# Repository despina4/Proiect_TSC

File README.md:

# Documentatie Hardware - Proiect Wearable / Smartwatch nRF52840

## 1. Diagrama Bloc

Diagrama ilustreaza doua fluxuri principale:
*   **Fluxul de Alimentare:** De la portul USB-C, prin circuitul de incarcare, catre baterie si apoi prin convertorul DC/DC catre restul componentelor.
*   **Fluxul de Date/Control:** Centrat pe microcontrolerul nRF52840, care comunica cu senzorii, display-ul.

---

## 2. Bill of Materials (BOM)

Tabelul de mai jos contine modulele principale folosite in proiect, impreuna cu link-uri pentru achizitie si specificatii tehnice.

| Nume produs | Ref | Link achizitionare | Datasheet |
| :--- | :--- | :--- | :--- |
| **nRF52840-QIAA** | U1 | [Component Search Engine](https://componentsearchengine.com/part-view/NRF52840-QIAA-R/Nordic%20Semiconductor) | [Datasheet](https://4donline.ihs.com/images/VipMasterIC/IC/NRSA/NRSA-S-A0021008244/NRSA-S-A0021008244-1.pdf?hkey=61A2E4C270F0397D049F8F05BD4F1054) |
| **BQ25180YBGR** | IC1 | [Component Search Engine](https://componentsearchengine.com/search?term=BQ25180YBGR) | [Datasheet](https://analytics.supplyframe.com/trackingservlet/track/?r=0x34EY99PS_gIu2qWuzU9_U842M9-un2szqNoXX0OQ9lqbiEKGN3BJ73jgvlrgiXR89Peb0evqc4GXoUXllBhv0EBbS6IvP2J9XlK2jP2A6stFn-y2dC_JwPYaasEzx0O-vxRsHrvjDMttJo6_R4oFWH3JMP3HPT3L-Nznne1h3KEsMXPl-eGs-pMLJ6GfjQCQ6HQMtq6htuNY6F9LyUZPlBJcp1K0CY8wZlcmYWeP3d00EKGkwMEYVuhGukZlpk9s5eB2sCQiAmMMBIBl2JypaU6-1_JfgzrT5bvUUGSdkUqZVMi7lvw7V03cGienT9feVSRMBhhWaNFGhzf6_3f8ZFIsqpCB6RNiXgzOy4UCL8GWfRIZFBGLsZvpqmkT4iLPnvXUrdv-uMDsMargLsNudyjFN55qoFIoM_lHR3jfZiBrXHrx7fYI1m3zFYuPc18lUM4dLxlLjbOFrCL0NYDVpEveG92dFwHfnYbXQgvjrXr2rAOwFVNwEcAFSYk5ktGr0AZVSeLG20ATU9f5Ua1VPDIn7dlK_upDe2HQ7ZnA50hRZ6l5EHTT1TR6mV6zah) |
| **DRV2605YZFR** | IC2 | [Component Search Engine](https://componentsearchengine.com/search?term=DRV2605YZFR) | [Datasheet](https://analytics.supplyframe.com/trackingservlet/track/?r=0x34EY99PS_gIu2qWuzU9_U842M9-un2szqNoXX0OQ9lqbiEKGN3BJ73jgvlrgiXR89Peb0evqc4GXoUXllBhv0EBbS6IvP2J9XlK2jP2A5_GZUU6ZJYL2OifsViLlEfO-vxRsHrvjDMttJo6_R4oFWH3JMP3HPT3L-Nznne1h3KEsMXPl-eGs-pMLJ6GfjQCQ6HQMtq6htuNY6F9LyUZPlBJcp1K0CY8wZlcmYWeP0ge5YXjaukObe0lIq9YZ1Y9s5eB2sCQiAmMMBIBl2JytG3z6cPnGe-cmO7h9dQIJ2kzUBKYJ3kKq1ql5kAIW4INEEo_wOFAtAhver6Q6kuIfVofA0tjpG_oIZ517f4Vb78GWfRIZFBGLsZvpqmkT4iLPnvXUrdv-uMDsMargLsNnX2hKYawPQ2D7SudtAUHHtiBrXHrx7fYI1m3zFYuPc18lUM4dLxlLjbOFrCL0NYDVpEveG92dFwHfnYbXQgvjrXr2rAOwFVNwEcAFSYk5ktqoT45GaC_RMx31tbcd0eeVPDIn7dlK_upDe2HQ7ZnA50hRZ6l5EHTT1TR6mV6zah) |
| **BMA423** | IC3 | [Component Search Engine](https://componentsearchengine.com/search?term=bma423) | [Datasheet](https://analytics.supplyframe.com/trackingservlet/track/?r=0x34EY99PS_gIu2qWuzU9_U842M9-un2szqNoXX0OQ9lqbiEKGN3BJ73jgvlrgiXR89Peb0evqc4GXoUXllBhv0EBbS6IvP2J9XlK2jP2A65Hh8cz60QZRR0eH2YQezA3QFuEZVrF44_bcvGN_lyh23KGb2OV452gy8_0y5ECrz838JB1AXz4HlagHjHKK0zIVUI_nXq20DP4qZVoZkXjzWM81fZaYscHPt3_tBNEt3RrwddE0Gz5nohvYrd6gxYc3LSeSqEPukqMV5glPuL1CNaI1kVMusAxJjzUp0G6CswwJW_ssfKVIHLQT-IJeMMwbXLDJpduD2PNPjtLS0y1srGxUCiKdKyCV91htNfRSMP3qWp9KAByolyr1E2K_PZ5B6aRPZ6alq5MnvhLx7KzpSpvK4vdnUllhspAmNRIPTvgHjblUHXdwUjCbyASDYb9MYvdijqaUwAnHrJsf3zmbjzHXjtwLXVovtyhuM6e6Ynw7vpRUSsWu0xJF95B32liScqep17qvTwnJG7pQnxHSR6-2eSgXb3qFP3Jk0Oamw51BA5ruLDXxwczn9SmJ5bdh_kmzVEzIYo-AC-eZSsAdcBnfKHuYtpsSdnOr0On6uXkGbg_xWe6X4FW8arIIpH) |
| **RT6160AWSC** | IC9 | [Component Search Engine](https://componentsearchengine.com/part-view/RT6160AWSC/RICHTEK) | [Datasheet](https://analytics.supplyframe.com/trackingservlet/track/?r=0x34EY99PS_gIu2qWuzU9_U842M9-un2szqNoXX0OQ9lqbiEKGN3BJ73jgvlrgiXR89Peb0evqc4GXoUXllBhv0EBbS6IvP2J9XlK2jP2A7oxjHvu3vjqv4WxQoBIehIpFdNxUOLInPyEkIhtPddHwvaXQpBCG-4NPHWS8Luf9PDHBq8VAfKRDCu-t4VKkJgw0q36_CHuXBQmQUFy7_kW1dsUOzQneFlP07hp6tEqIRtrF0F5Zb_nR1t-hLLccIBUGxWBuEpEl7kUFZ6dE5hS-7kEI0Imii-UkRj2fTw2ElN8-A1nBG9hKzVKn06I4IowPKk5xXTOIwLAB724T4UUPVC2PjCMrZrSZdNsHPTjWe6k3zgMkqRJAhHbiU-gTTV8piVEtXZSzcLQMzYFvj83r7hfL_VtnnBJVZtCWXJKkLcTeL-qC6Kw-bbZFGwqn1eTorqzedjC01O_9x4TSWbk5yQDrvZUK-iGRXtGqr6qwa0P7iXpgr0HPlvis6ez45oylOW77ENVj4BRgrI885Q_XvOL-xgY1EhwCaKTrd3oN5is0EaxHlNGM4zz0QyxhvBvl-geXlL_R-njMpWcd0RKFtHWMev1NGVlnzxgiu0SjMG-5Cr55kPMae_7V9Vf5dfvXk1u41AF-eDZgjn1NFilA) |
| **MAX17048G+** | U3 | [Component Search Engine](https://componentsearchengine.com/part-view/MAX17048G%2B/Analog%20Devices) | [Datasheet](https://analytics.supplyframe.com/trackingservlet/track/?r=0x34EY99PS_gIu2qWuzU9_U842M9-un2szqNoXX0OQ9lqbiEKGN3BJ73jgvlrgiXR89Peb0evqc4GXoUXllBhv0EBbS6IvP2J9XlK2jP2A6DXbvJdRmZW2yJtFQ1_uB8CpVVRsuy5H3f7RjpWY5KE02ZSejBQ-1sTThh8ZhaVmPyvNMTfmvWqPHCxujzIU_9L5QMgSVsWqB7UcVIWqkZMCBUsKvx5VN_Ff7UgqURIux-A-P-bJZx2uYoMIaFEdYZKxLQSmqRADJVv0bC3pADlsMXLGPj7wuD_4oozecdZ0K-8Axqnk-A4H62ngUFyJ-u_KU29-JDjkr_a4X5kD-SwJaXo8CyXJYulMKyYA9Ww-0YTP0WJ4WexDOETYGOo7QYWrTP3cuO2jaBxtmnP_QmXvwZZ9EhkUEYuxm-mqaRPiIs-e9dSt2_64wOwxquAuw2wbj8YtdMq1G5JGMGXucSqWIGtcevHt9gjWbfMVi49zXyVQzh0vGUuNs4WsIvQ1gNWkS94b3Z0XAd-dhtdCC-OtevasA7AVU3ARwAVJiTmS3yOHNszfnmm1dqoJi-2CiH_5iJolc-gxDtjl0RWrOjUc2y34iccbFKo6BQ_BAC8ZA) |
| **USB4105-GF-A** | J4 | [SnapMagic](https://www.snapeda.com/parts/USB4105-GF-A/GCT/view-part/?ref=search&t=USB4105-GF-A&ab_test_case=b) | [Datasheet](https://www.snapeda.com/parts/USB4105-GF-A/GCT/datasheet/) |
| **503480-2400** | J1 | [Component Search Engine](https://componentsearchengine.com/part-view/503480-2400/Molex) | [Datasheet](https://analytics.supplyframe.com/trackingservlet/track/?r=0x34EY99PS_gIu2qWuzU9_U842M9-un2szqNoXX0OQ9lqbiEKGN3BJ73jgvlrgiXR89Peb0evqc4GXoUXllBhv0EBbS6IvP2J9XlK2jP2A4bhBcp5m93QVvXq-b4ZvXprUYNzIdppOCDGuJ7aDflaky8671aiqchDLLtbVjC9xdCaJJ6nF0pYtLKaCopUVPbENE6D3pzXoxhUvdbzuW6oJXfd1FVm63N6SPCyX6r1R5v9WVM0GlwVZLnxlj5hrMZy4odeEzEID3f9KwH_MHnqtKpOLWlH5R74gzWY8AYOo5GMjISf0eMdYvE6MODW1eb4kLz15caNHBYeIVK5MK9qSpUczJXWYrJFJGp6PnnEax_T5A32QcD4zvMW-ssnnZd4OhSZlAx9pe7i1e8hrw58wOHOyfVNVOXSLomvqnUeGmBnnj8VHAk7jgVz6Pxql9q4VLXOsw1zGQSjIjD0YczTpyQDrvZUK-iGRXtGqr6qwa0P7iXpgr0HPlvis6ez45oYMjPU0esZvj56AyDu6TV43vOL-xgY1EhwCaKTrd3oN5is0EaxHlNGM4zz0QyxhvBvl-geXlL_R-njMpWcd0RKFtHWMev1NGVlnzxgiu0SjM64VUgM7uRV37HYPQ2vpo0llXHrUb_2BeaRI1zgnEpSA) |
| **EVP-AKE31A** | SW_x | [Component Search Engine](https://componentsearchengine.com/part-view/EVPAKE31A/Panasonic) | [Datasheet](https://analytics.supplyframe.com/trackingservlet/track/?r=0x34EY99PS_gIu2qWuzU9_U842M9-un2szqNoXX0OQ9lqbiEKGN3BJ73jgvlrgiXR89Peb0evqc4GXoUXllBhv0EBbS6IvP2J9XlK2jP2A7jRNlQCGFKUCB9Om2oIPVb8wB-QC4Y0LpnCr5Xq_ByDC5GEiqgkeKxStY5Iu4CVibuldEG2BjB5lNvto04wXg8jGQATYHCL6DopdSbrdwi56E6tw2YzEoN2JK_GY31dBUUo3LDYzCtu7wIFWHSy5ldFUMm7nZxbAbVY0l3I7ewOZYX363B6_l_RD2rR4C4K-my9KZLIZBsuzkxb3A5MS3NsEKKVZJUvtL97I9b8a5mIzliD9eDRpt3ctCvjuas-AASRFTRlsq83k9cscG5Zi-TsUcA-0LBtlakk22B3qKjpagoB0KIBYTkXeQHEqE58jyRQGb7iM-fmdBd-zqmHjtKd_NmoHXgB5duqrDZJlY4H5yQDrvZUK-iGRXtGqr6qwa0P7iXpgr0HPlvis6ez45o2VHowPjIDZTEf8wGRQ4ci3vOL-xgY1EhwCaKTrd3oN5is0EaxHlNGM4zz0QyxhvBvl-geXlL_R-njMpWcd0RKFtHWMev1NGVlnzxgiu0SjOjOFfjEDKuI85CkEY44YiXAqRNgBm1QPZfXRUNd55gVA) |
| **2450AT18B100E** | ANT1 | [Component Search Engine](https://componentsearchengine.com/part-view/2450AT18B100E/JOHANSON%20TECHNOLOGY) | [Datasheet](https://analytics.supplyframe.com/trackingservlet/track/?r=0x34EY99PS_gIu2qWuzU9_U842M9-un2szqNoXX0OQ9lqbiEKGN3BJ73jgvlrgiXR89Peb0evqc4GXoUXllBhv0EBbS6IvP2J9XlK2jP2A5CBZpEZS1QpXV8FFu44G8mfHuYmg61LS2zWxuqTvB9fpXV375gtD9bFmcCH2H2-DAuRhIqoJHisUrWOSLuAlYmG3OIjmksJ1dRyGU5ZtR5ygKEZn7IXrj9HCDF2qCHjmkMrQBkA8LW1ZVPP8ECLfGEq3PUbV5s03lneGIiPby_jK-PplrsL5DHOAlCUT_Isuz2zl4HawJCICYwwEgGXYnKR7O9_Lww0zeRhLdSHLfmKLGvvXkZ69BbN2cqUVuLZwWkzHNmVRqmDRdD2bTu63RwJxUArrnlVYIvOowP0A2ooJyQDrvZUK-iGRXtGqr6qwa0P7iXpgr0HPlvis6ez45oA6DbeayHRodKseYDStLS-HvOL-xgY1EhwCaKTrd3oN5is0EaxHlNGM4zz0QyxhvBvl-geXlL_R-njMpWcd0RKFtHWMev1NGVlnzxgiu0SjN1C5tMR-D4l4QIlPKj2IZ-Yy9VWewJTIBnNBaBqDAucmok7ZMY6ahHbaLYDtLSQSg) |
| **02016D105KAT4A** | Cap | [Component Search Engine](https://componentsearchengine.com/part-view/02016D105KAT4A/Kyocera%20AVX) | [Datasheet](https://analytics.supplyframe.com/trackingservlet/track/?r=0x34EY99PS_gIu2qWuzU9_U842M9-un2szqNoXX0OQ9lqbiEKGN3BJ73jgvlrgiXR89Peb0evqc4GXoUXllBhv0EBbS6IvP2J9XlK2jP2A7nZAqH6w5fKchKrnD5jWCWB9uu1cFEpsbINa2EvY3xALGo-iAVS7h3PyuKIuP0uNZtyhm9jleOdoMvP9MuRAq8_N_CQdQF8-B5WoB4xyitMyFVCP516ttAz-KmVaGZF481jPNX2WmLHBz7d_7QTRLdwdqbPKSozx2UncdATv8f8tXMySboAvDMsIjBRKwEr_Q2jLNScnH_dLxDrjv1EkHNMMCVv7LHylSBy0E_iCXjDMG1ywyaXbg9jzT47S0tMtbKxsVAoinSsglfdYbTX0UjdS3r3VBQI1vaml90w1YXmOZwvE2zhk6aceLOkr7DbpYy5Q4LxAI48xDMx_XnZmHh_fuDZ1JjOvgaKgrvl3RWpnkNWF_MCUOTM_XXPqM7bQP8GWfRIZFBGLsZvpqmkT4iLPnvXUrdv-uMDsMargLsNqbHJnjKIKwWJs5Y8BBPlGdiBrXHrx7fYI1m3zFYuPc18lUM4dLxlLjbOFrCL0NYDVpEveG92dFwHfnYbXQgvjrXr2rAOwFVNwEcAFSYk5kt9N8XAFyUPAGbflqS7VyAcxuzNsnrGaIyGIlhKp9g4wTmDKwPnl8GHxC8271ufp6a) |
| **0402B472K500NT** | Cap | [Component Search Engine](https://componentsearchengine.com/part-view/0402B472K500NT/Guangdong%20Fenghua%20Advanced%20Tech) | [Datasheet](https://analytics.supplyframe.com/trackingservlet/track/?r=0x34EY99PS_gIu2qWuzU9_U842M9-un2szqNoXX0OQ9lqbiEKGN3BJ73jgvlrgiXR89Peb0evqc4GXoUXllBhv0EBbS6IvP2J9XlK2jP2A5dXweU-D0sdBl1Qjp1-TAk_mVbiV46egqumwUGPF1lPZOKh6TrHICN8puILsKgsK-sQYSYGHAdrwcZ8E3HkBuRqTzZoYvrcDuK6DczS8PHjtCeG-EZDmaKILRgGXnDovSJdSjTWfIdrOBLyjZVWwqbU8QHBZonHiX1ulf1ijnuV7zT-G6CvmssDKjz6ykjyiiOL6l3SGqOLFDw0gOobHbOqHuUYKiE61kjf205L08i3UM0rohfI1WiHrOQi4HMOm09cQB_Eb5GLgSyk-l9ROWJYnHwneW9h_i_wyqbadWvI2fq1mxS8j8a2gzW5h7Am3q22IuGOtCVzPmDh8SvQTkQ758gNK6-fDp2DK2st6xkFXHiipFVag1_ybNPdjfdaX1UzwWSBXnGX2GnGPz7GnffHFOReOLDLMKa5h6Mh-WEPbjzHXjtwLXVovtyhuM6e6bvcO-Aa1fTPjORUyGtfwzUiScqep17qvTwnJG7pQnxHSR6-2eSgXb3qFP3Jk0Oamw51BA5ruLDXxwczn9SmJ5bdh_kmzVEzIYo-AC-eZSsAe9gIh7dial-5XlJgFXLBC6nnoq1N-30oEqZ652mt86F5eSLo1vpaeRbZ2kk2sM_6fNceAboe8iJs_NcXwRFbjbfHFWQBRwq8Bz1Vz6F9ml2) |
| **0603N101Z160PHT** | Cap | [Component Search Engine](https://componentsearchengine.com/part-view/0603N101Z160PHT/Knowles) | [Datasheet](https://analytics.supplyframe.com/trackingservlet/track/?r=0x34EY99PS_gIu2qWuzU9_U842M9-un2szqNoXX0OQ9lqbiEKGN3BJ73jgvlrgiXR89Peb0evqc4GXoUXllBhv0EBbS6IvP2J9XlK2jP2A6bBUHyoIFXnx--EZGBFfQnKj-pGIWglMqjPvjnZMI1ROD-eFH0dQ5fGmWruxh3uWLiRxa5GVb1G8SarLAYvRwVCvh2rsM5Co0LiTQuRgHYQmR_Kw-WhaAp18Vd6BkulhiUYsFGfOjiEUo_G-gOSQISOb3asDTRa2nbQgBadcJRBn3xHAfo5WBcsZgsl-SCWdzDkyf7vNUEDwBZtcUDHi-uKY0hwe4a1bnvo8zMtwGo2MaC01xwDDOzSc4VyYfJSx1PmhpZFwWuDduo_rie84KN2CwC3n1Orhmp14oyntM5qhJlmUpo6uFqXElS5tKGkuIQjmR3i9tKd6_YkPcb9R46EjUq7dccUQLL8HwYZhkm03p4hv0lEuMHqdICzl8lNaNDQCtx65VM_jqpqYqe0JUmllCn3E-KeQ11zr8yAYxvqRTZ7oMUBpCdo4N39FcT7YRWXg_A396EZyMOfkdF4xaWlNX1rVIRRUxnnMVvpiJ9xJJy0_ZKSkvi3-FXIP0bgnv26jPEkRvUWmwZ5lajK99ISxh5QC76NAKNcG2MIA-8IA) |
| **MBR0530** | D_x | [Component Search Engine](https://componentsearchengine.com/part-view/MBR0530/MCC) | [Datasheet](https://analytics.supplyframe.com/trackingservlet/track/?r=0x34EY99PS_gIu2qWuzU9_U842M9-un2szqNoXX0OQ9lqbiEKGN3BJ73jgvlrgiXR89Peb0evqc4GXoUXllBhv0EBbS6IvP2J9XlK2jP2A7wO1xHkSqzgcdOiv4DyA6-KUE0hnO-8Oq0TiydnN6_P0wUQHFX21cOqvJTns1cls8glPBTBkJaHrq7uCkVkwGv-5pj5AVwFB9sB-wcL2FFgyWVm9T9cIRr8wx2IAUmRLrqcyqWpNEiSB4NqE89sevkbBDFmKOLKGgFGVXUbq7BdmiOYInF50iH-ZETGnBwi_rX5nalc0YozzZXH0Ho6mrv8yOBDBMkcmmw7t-R5Pp9YtrlefXbBe-6T8WCNg08grwHzDyjqT6SUcaAWVlKnh6bRiWE1TJKU_uvvFWX1OPSqvoIi470E_jmy5w33-r2mBKtQHk8z5wpru9bm3kq9Cy6uPMdeO3AtdWi-3KG4zp7pgB5vSuVZ0lZr58FJvreOv6JJyp6nXuq9PCckbulCfEdJHr7Z5KBdveoU_cmTQ5qbDnUEDmu4sNfHBzOf1KYnlt2H-SbNUTMhij4AL55lKwBuVAU7zPQxXbQZLEQMKWD6P2ReE9xXD9nOJFwSVA5qyg) |
| **USBLC6-2SC6Y** | D3 | [Component Search Engine](https://componentsearchengine.com/part-view/USBLC6-2SC6Y/STMicroelectronics) | [Datasheet](https://analytics.supplyframe.com/trackingservlet/track/?r=0x34EY99PS_gIu2qWuzU9_U842M9-un2szqNoXX0OQ9lqbiEKGN3BJ73jgvlrgiXR89Peb0evqc4GXoUXllBhv0EBbS6IvP2J9XlK2jP2A6dTUnJ4j6IQujKF6av25-uRn4mg0r6kCfWETOQX8TpiO3zYIcPoaq5tD5T48ppj9PKEsMXPl-eGs-pMLJ6GfjQDAOKFUEpEDhTaSRRNqlFXNPTmxA8IAfp4JgYg0H3dX0S2Rl5Z4YAKcDbbf2FiaTyJGaASMXUOk9RWMrzJNXv0e9LeTd8fSBTQIhQLd_oSdd4n35WM1T5BDS4jAG809kCU9qHdpI_P1FtEJcxAylr-UUxFk_RBQjjQqRh_5gqISyEbE4wKs2WMG7h72Ep3QaU6fJ-ZcDnJd5iSK_QW5dHq0HEicnlBgfQPpvg0syCaHmVKFwNUTFYIlDkTOzLnSyg14emPykRQ2HA1I7ujpckpIN2GnVYqOYsJ-lsbaAvme0sVyGrswj3lfibNR5l-0ftpPMQLSbextwMh8I3CKooxV56I7DBspNPCsMutOqdCUSSPYfNBouPZ7bBLacZbiLD_wc8b_cyrm1urcwAFPlI0xblue5FN0zsoVKEknwfuYOR5hxeUZWeYVWUO6LUK4_8wUrAjT-b3Sjy-0bP1XwWWTLPURn-ARKBsvhsbTH7CGg) |
| **HT7750A SOT23-3** | Q1 | [Component Search Engine](https://componentsearchengine.com/part-view/HT7750A%20SOT23-3/Holtek) | [Datasheet](#) |
| **SI1308EDL** | Q3 | [Component Search Engine](https://componentsearchengine.com/part-view/SI1308EDL-T1-GE3/Vishay) | [Datasheet](https://analytics.supplyframe.com/trackingservlet/track/?r=0x34EY99PS_gIu2qWuzU9_U842M9-un2szqNoXX0OQ9lqbiEKGN3BJ73jgvlrgiXR89Peb0evqc4GXoUXllBhv0EBbS6IvP2J9XlK2jP2A6AMyAqhHVNKsGe3pXOcOS5GeUpnYTHKSU1tSdDUz28FcNYpvUwKkT6-1c90QkYZSjiRxa5GVb1G8SarLAYvRwVCvh2rsM5Co0LiTQuRgHYQmR_Kw-WhaAp18Vd6BkulhikC5vKqqu6V1EFJidUD_ufSkG0Zqo_Donvb5lVpWg0LT8A45ry3_lFEX0GZ_8_Hf1y738B_yDR8i-TXfcSmkd9w5Mn-7zVBA8AWbXFAx4vrimNIcHuGtW576PMzLcBqNjGgtNccAwzs0nOFcmHyUsdYWKVr5xUmpj_cEc98aoKnjvFBG7Te_TQWkEG5a2F79tW_A3ziws0s-fKjT7xdGFXCVZ5A2CTPdwyzKRuzXR4dRqZ5fC_9uoGzVmOxbyyvbN2SygWLApeagXDewU6Pk1dAJZw2q4h0oO9onbBmQwOgELMRzOCoN9cRB6wuyIlPj5cU1-C3stG4f02YzfyJ5AcSrLEYWLqR3hfojQpMdAuDb5XxeXJ6Q-0EJTyAN08GE6pEvvQQaaDiDZnDSaMvTi_jJTd1ASKLIri-KACGiFw5s3OsegO5ItH7__7DcEr5_I) |
| **NX2016SA-32MHZ** | X1 | [Component Search Engine](https://componentsearchengine.com/part-view/NX2016SA-32MHZ-EXS00A-CS11336/NDK) | [Datasheet](https://analytics.supplyframe.com/trackingservlet/track/?r=0x34EY99PS_gIu2qWuzU9_U842M9-un2szqNoXX0OQ9lqbiEKGN3BJ73jgvlrgiXR89Peb0evqc4GXoUXllBhv0EBbS6IvP2J9XlK2jP2A48l0WG0Kz9BgjTuXWxdN5J9PrPuoDYzNb8HGtnWQsQCtRy09GjV1QknTHaAFhBfl5MvOu9WoqnIQyy7W1YwvcXQmiSepxdKWLSymgqKVFT2xDROg96c16MYVL3W87luqCV33dRVZutzekjwsl-q9UeFDaHa2jUBBPEHp7ed-AKdkuiDrUeTQqvLY-LqAyhM0Doq08edgAP-RndstM7_Ls2aITaeKAAvMzhmqOxsiEoX-JC89eXGjRwWHiFSuTCvakqVHMyV1mKyRSRqej55xGsf0-QN9kHA-M7zFvrLJ52XXBFGtMKxb2desZUgDSkqdVIuba9AUcrgEI6_j7RQ66203XD85CxQQSsVvcBRIdytK2AaQ-VL0OGtCmjrTRti2YoCQS1GDr0JJM1dN-mDsX6pmmOOGsGx_VmPPwsiNLQG5lAn0LI95I6I_EqNKvC_TDvcGmUmJ-5ITz8upunwSiNgQpDlKIHg2kyQQSrZJQiJ6uO9sE4jOHL-0LxbwJlyeOtP9gXMSuREOJ0ZugpMfUtGuNVeHihgMHsfNQYTS5NRYZnMRjkNNIvl6kBKsvWRqpOkOL8G-Cd7UJr8ezYznOUyAQz4_8lqFRyrrVNfyCt6w) |
| **ABS07-32.768KHZ** | X2 | [Component Search Engine](https://componentsearchengine.com/part-view/ABS0732768KHZT/ABRACON) | [Datasheet](https://analytics.supplyframe.com/trackingservlet/track/?r=0x34EY99PS_gIu2qWuzU9_U842M9-un2szqNoXX0OQ9lqbiEKGN3BJ73jgvlrgiXR89Peb0evqc4GXoUXllBhv0EBbS6IvP2J9XlK2jP2A6OOEVw15QP7tPUvP4Irtf8s4ZIMSZB2FkK3z5BQbDnQeIw-raJdkBZGeCdPWUJKtp5DbdaDd6CcWrKHvbRpzWSw8KiG-khtgpu_T7PNDBLvWIHJTy10X7VGYJNtoJkJ9ngJWvyW0-80hwI5BDU_8GiC6bkD6J99vtIvtDuHJ7h_awwAxDTN2Ggk8_aEL7xK_jo7sNLAFiaZjg7nl6Ovgxmw3fPvkMtY1LXllfQxZL74KZpjjhrBsf1Zjz8LIjS0BuZQJ9CyPeSOiPxKjSrwv0wa7loom7alaCyupGP0N3RLYEKQ5SiB4NpMkEEq2SUIierjvbBOIzhy_tC8W8CZcnjrT_YFzErkRDidGboKTH1LRrjVXh4oYDB7HzUGE0uTUVp8R2sfm70KP0jqqx_G84Jd7ThPhDqJEdDf4PpViTvuptsIJTT83JkTMKMPalQcw8) |
| **WE-TPC 4828** | L5 | [SnapMagic](https://www.snapeda.com/parts/744043004/W%C3%BCrth%20Elektronik/view-part/?ref=search&t=WE-TPC%204828&ab_test_case=b) | [Datasheet](https://www.snapeda.com/parts/744043004/W%C3%BCrth%20Elektronik/datasheet/) |
| **MLP2016SR47M** | L7 | [Component Search Engine](https://componentsearchengine.com/part-view/MLP2016SR47MT0S1/TDK) | [Datasheet](https://analytics.supplyframe.com/trackingservlet/track/?r=0x34EY99PS_gIu2qWuzU9_U842M9-un2szqNoXX0OQ9lqbiEKGN3BJ73jgvlrgiXR89Peb0evqc4GXoUXllBhv0EBbS6IvP2J9XlK2jP2A5Kwy3vc7YdoE68w7NKwhDwRn42K-SSfDC_whUysKXwOqk82aGL63A7iug3M0vDx47QnhvhGQ5miiC0YBl5w6L0iXUo01nyHazgS8o2VVsKm1PEBwWaJx4l9bpX9Yo57lcPvK3VYxb21XU9xi-kpmghnpvZuCWtXO9Y4OGC9EpI9bk2U_7S4GrNEyIHF4YyuwK9qP4ZSn_IsAHD7RAedt2tPXEAfxG-Ri4EspPpfUTliWJx8J3lvYf4v8Mqm2nVryNn6tZsUvI_GtoM1uYewJt6pzb7LzUuFGKhPqJRUYm2NOPQVqJ6A84ywzr6Pa2mkL8aEfSSo0qYfXIQ0KZoaPL86m-DvPzuMkx6FOJMoLnQ9SVtCzQwCDFF9dk6kD1guS_4Jx24QVGFuSzG5RTnkE0jETSQhAWFvmGM0YcRWb4wcVG_FCT5MCRw7Pj1mZ5EnW2av6bI8oZWX0MtSQiC4UaxypxO1X7E28hI6RZelPetP1kBH2H5xhz565LJ7dSQERxr1_KEZZBGck-ScrZgI0vwyPehwRChAqP9YNYtj0KbsLrv6rgOwya0xQOL4WWyt5Q) |

---
## 3. Detalii Tehnice Hardware

### A. Centrul de Procesare si Comunicatie
*   **MCU Nordic nRF52840:**
    - System on Chip -> gestioneaza stack-ul de comunicatie Bluetooth 5.0, procesarea semnalelor de la senzori si controlul logic al alimentarii.
*   **Conectivitate:**
    - Include ANT1 pentru transmisiuni BLE stabile, cu o zona de decupare dedicata in planul de masa.

### B. Subsistemul de Afisare si Interactiune (UI/UX)
*   **Tehnologie E-Paper (SPI):** 
    - Ecran bi-stabil pentru a elimina consumul de energie in mod static. Imaginea ramane pe ecran fara alimentare (economisire pana la refresh).
*   **Feedback Tactil (I2C):** 
    - **DRV2605** actioneaza un motor de vibratii tip ERM, astfel permite  notificari tactile.
*   **Control Manual:** 
     - Navigarea este realizata prin 3 butoane mecanice, switch-urile.

### C. Detectie Miscare si Monitorizare
*   **BMA423:** 
    - Senzor inteligent -> pedometru 
*   **FuelGauge:**-> determina procentul de incarcare al bateriei
### D. Alimentare + Protectie
* **Charger** 
    - Incarca bateria prin USB-C si o protejeaza.
* **DC/DC**
    -  Mentine curentul fix la 3.3V pentru toate piesele.
* **Dioda**
    - Protejeaza placa de socuri electrice la mufa USB
---

## 4. Alocare Pini nRF52840

| Pin | Semnal | Functionalitate |
| :--- | :--- | :--- |
| **P0.00 / 0.01** | XL1 / XL2 | Conexiune cristal  |
| **P0.02** | SCK | SPI Clock  |
| **P0.03** | MOSI | SPI Data MOSI |
| **P0.05** | EPD_CS | SPI Chip Select |
| **P0.08** | IMU_INT1 | Intrerupere 1 -> senzor BMA423 |
| **P0.10** | ALERT | Semnal de alerta sistem |
| **P0.15** | EPD_DC | SPI Data/Command |
| **P0.16** | EPD_RST | Reset hardware Display |
| **P0.17** | EPD_BUSY | Status Display|
| **P0.18** | RESET | Reset sistem  |
| **P1.00** | SW_ENT | Buton ENTER|
| **P0.13** | SW_UP | Buton UP|
| **P0.14** | SW_DN | Buton DOWN|
| **P0.11** | PMIC_INT | Intrerupere management baterie|
| **P0.12** | HAPTIC_EN | Semnal Enable driver haptic|
| **P1.08** | IMU_INT2 | Intrerupere 2 -> senzor BMA423|
| **P0.06** | SDA | Date I2C |
| **P0.07** | SCL | Clock I2C. |

---
## 5. Design 
- Rutarea am realizat-o manual, pe 3 layere :TOP, BOTTOM, GND.
- In momentul generarii planului de masa (GND copper pour), am creat o zona de cutout polygon in dreptul antenei.Am luat aceasta masura  pentru a preveni ecranarea sau  detuning ul antenei de catre planul de cupru adiacent.

## 6. Erori DRC marcate ca APPROVED
Din cauza dimensiunilor foarte mici, am dat approve la cateva erori manual, ignorand erorile DRC :

*   **Copper Clearance (IC2):** Am acceptat 4 erori pentru a permite width de 0.3 mm pentru power traces (VBUS, 3V3).
*   **Via Overlap:** Pentru a conecta componentele din mijlocul componenetelor, cat si cele care nu erau accesibile altfel, am fost constransa sa pun via-uri peste componenta. 
---

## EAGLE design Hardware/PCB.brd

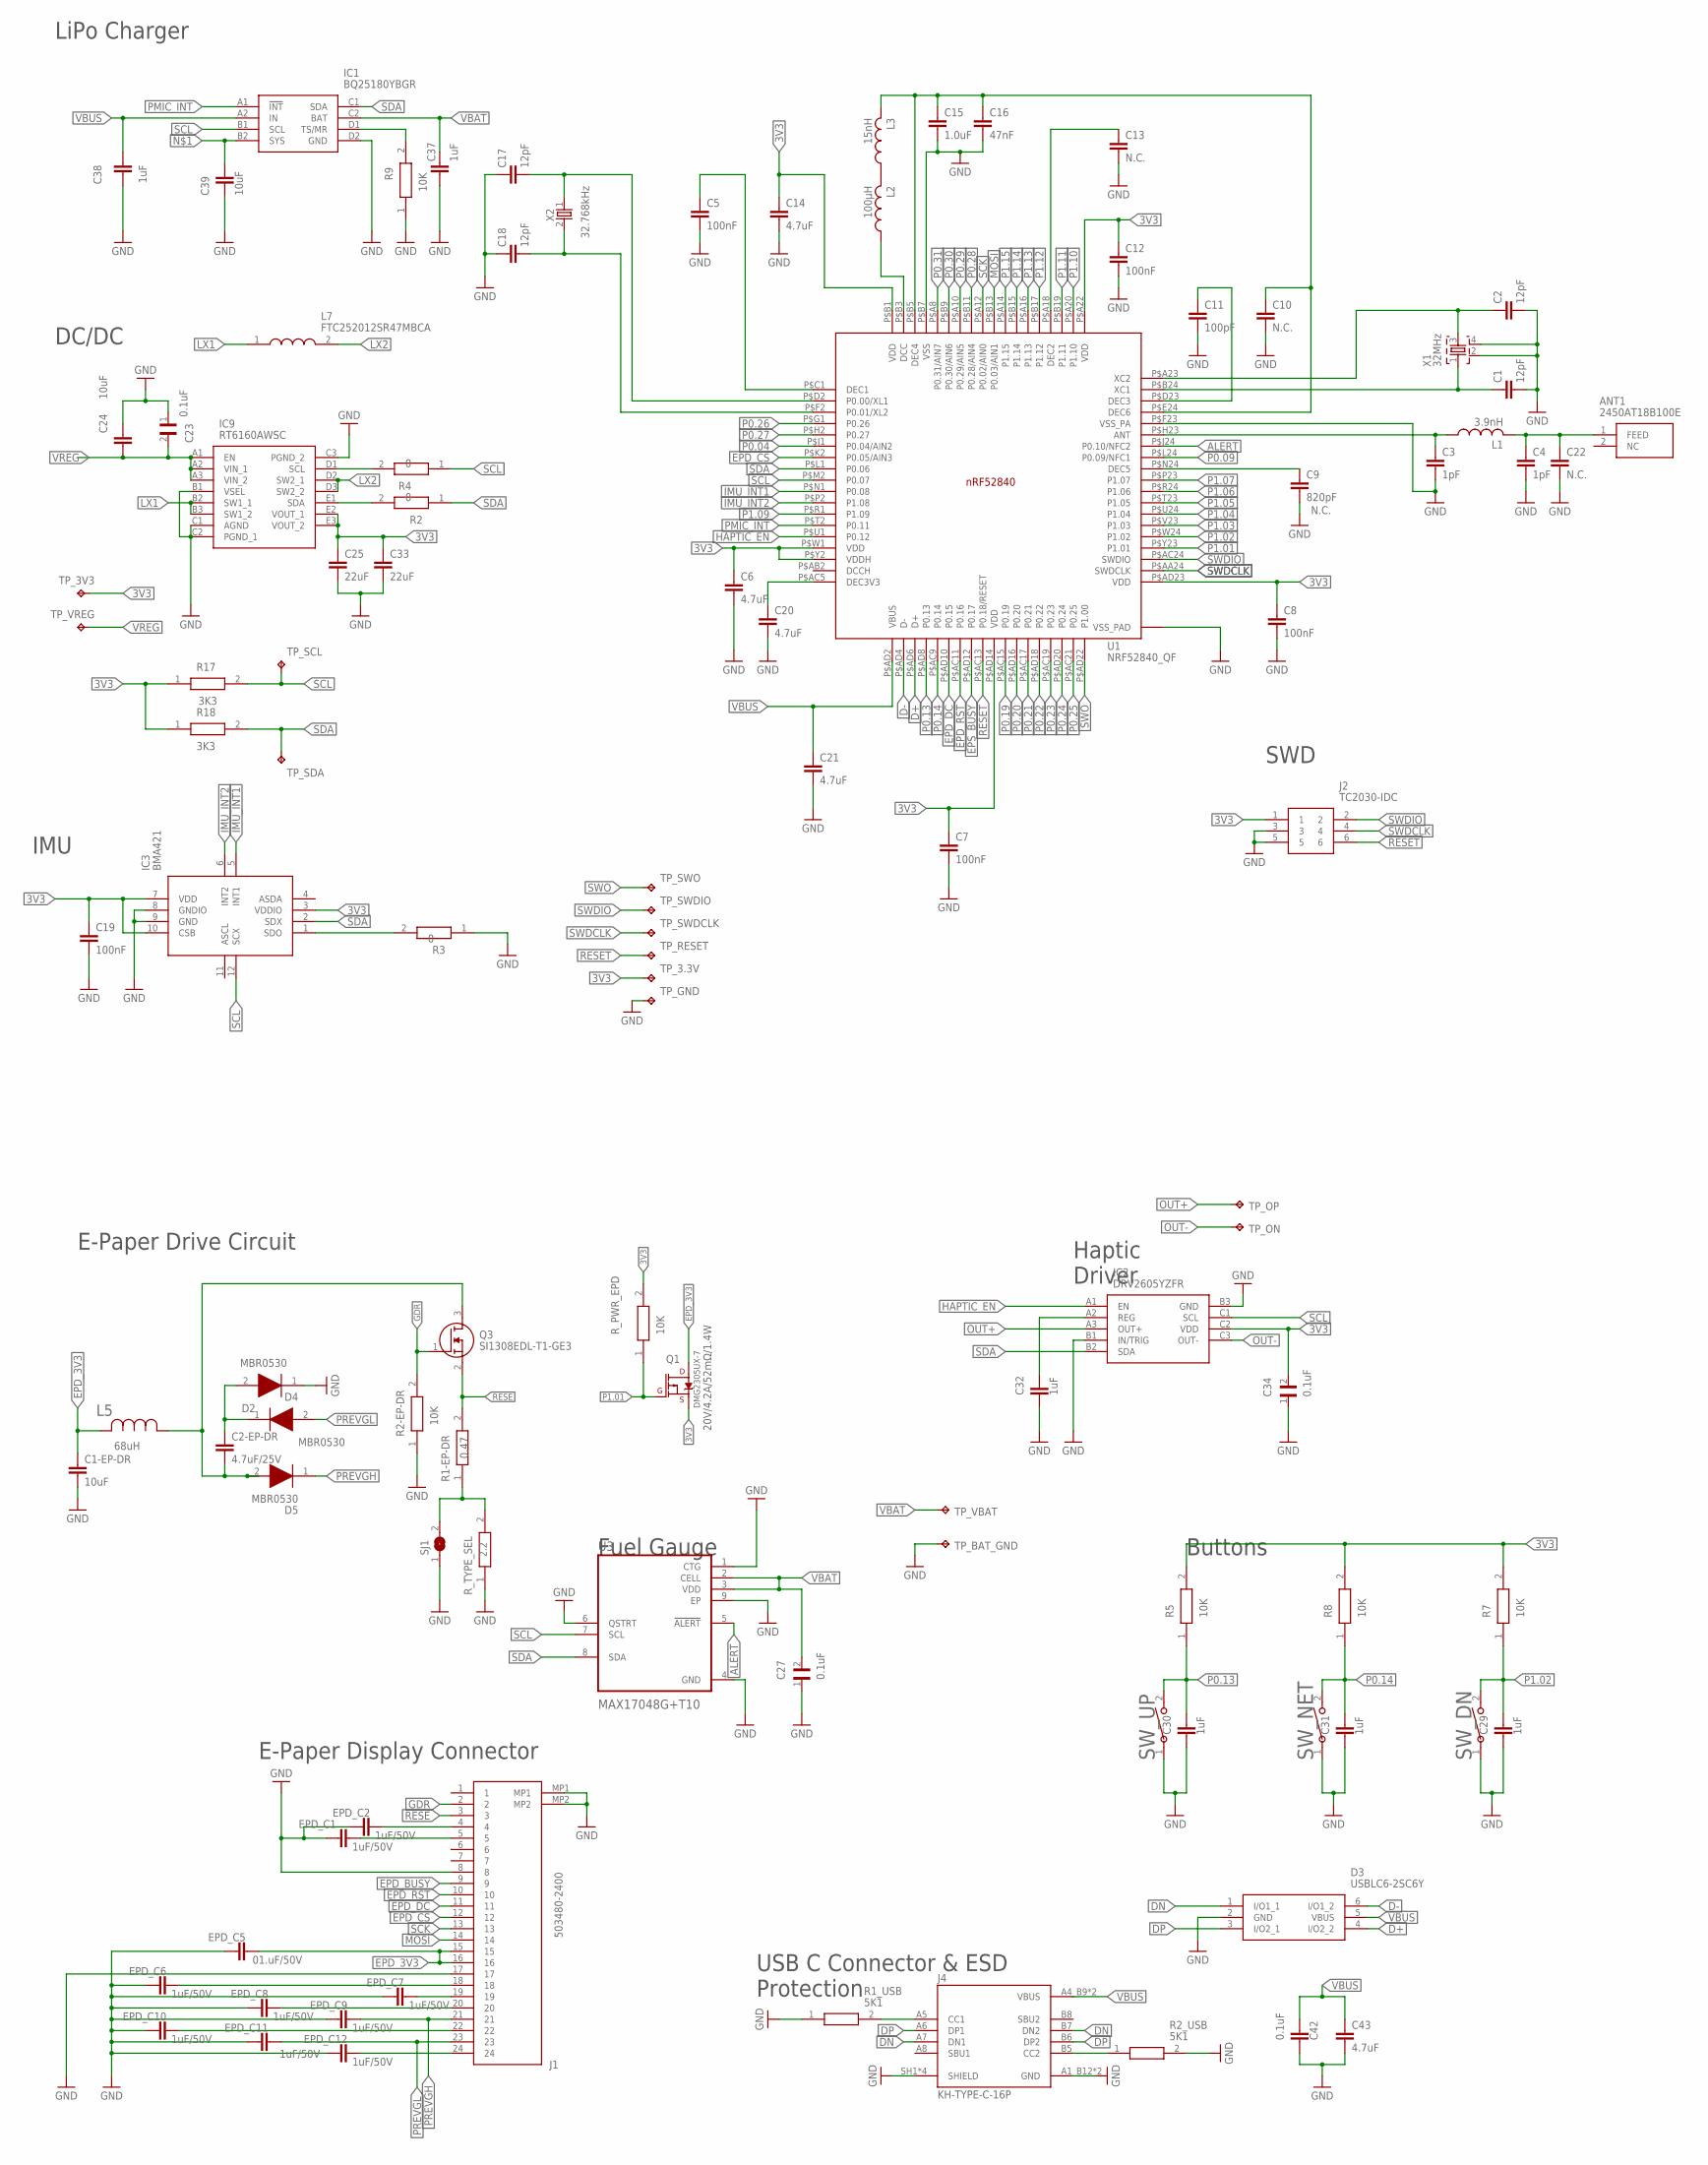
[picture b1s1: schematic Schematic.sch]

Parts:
ANT1: 2450AT18B100E; 2450AT18B100E_ANTC3216X140N
C1, C2, C17, C18: 12pF; NORDIC_NRF_3_RESC0201_L
C1-EP-DR: 10uF; NORDIC_NRF_3_RESC0201_L
C2-EP-DR: 4.7uF/25V; NORDIC_NRF_3_RESC0603_M
C3, C4: 1pF; NORDIC_NRF_3_RESC0201_L
C5, C7, C8, C12, C19: 100nF; NORDIC_NRF_3_RESC0201_L
C6, C14, C20, C21, C43: 4.7uF; NORDIC_NRF_3_RESC0402_M
C9: 820pF; NORDIC_NRF_3_RESC0201_L
C10, C13, C22: N.C.; NORDIC_NRF_3_RESC0201_L
C11: 100pF; NORDIC_NRF_3_RESC0201_L
C15: 1.0uF; NORDIC_NRF_3_RESC0402_M
C16: 47nF; NORDIC_NRF_3_RESC0201_L
C23, C27, C34: 0.1uF; GRM011R60J152KE01L_2_CAPC0201X13N
C24: 10uF; NORDIC_NRF_3_RESC0402_M
C25, C33: 22uF; NORDIC_NRF_3_RESC0402_M
C29, C30, C31, C32, C37: 1uF; NORDIC_NRF_3_RESC0402_M
C38: 1uF; NORDIC_NRF_3_RESC0402_L
C39: 10uF; NORDIC_NRF_3_RESC0402_N
C42: 0.1uF; NORDIC_NRF_3_RESC0201_L
D2, D4, D5: MBR0530; ESP32_C6_LIBRARY_5_SOD3716X135N
D3: USBLC6-2SC6Y; ESP32_C6_LIBRARY_3_SOT95P280X145-6N
EPD_C1, EPD_C2, EPD_C6, EPD_C7, EPD_C8, EPD_C9, EPD_C10, EPD_C11, EPD_C12: 1uF/50V; NORDIC_NRF_3_RESC0603_M
EPD_C5: 01.uF/50V; NORDIC_NRF_3_RESC0603_M
IC1: BQ25180YBGR; BQ25180YBGR_BGA8C40P2X4_100X155X50
IC2: DRV2605YZFR; DRV2605YZFR_BGA9C50P3X3_144X144X62
IC3: BMA421; BMA423_BMA423
IC9: RT6160AWSC; RT6160AWSC_BGA15C40P3X5_140X230X60
J1: 503480-2400; 503480-2400_5034802400
J2: TC2030-IDC; TC2030-IDC_TC2030IDC
J4: KH-TYPE-C-16P; KH-TYPE-C-16P_KINGHELM_KH-TYPE-C-16P
L1: 3.9nH; NORDIC_NRF_2_RESC0402_L
L2: 100µH; NORDIC_NRF_2_RESC0402_L
L3: 15nH; NORDIC_NRF_2_RESC0402_L
L5: 68uH; ESP32_C6_LIBRARY_2_IND_4828-WE-TPC_WRE
L7: FTC252012SR47MBCA; MLP2016SR47MT0S1_INDC2016X100N
Q1: 20V/4.2A/52mΩ/1.4W; ESP32_C6_LIBRARY_4_ESP32_C6_LIBRARY_4_ESP32_C6_LIBRARY_4_ES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
Q3: SI1308EDL-T1-GE3; ESP32_C6_LIBRARY_6_SOT65P210X110-3N
R1-EP-DR: 0.47; ERA-1AEB3401C_0201
R1_USB, R2_USB: 5K1; ERA-1AEB3401C_0201
R2, R3, R4: 0; ERA-1AEB3401C_0201
R2-EP-DR, R5, R7, R8, R9: 10K; ERA-1AEB3401C_0201
R17, R18: 3K3; ERA-1AEB3401C_0201
R_PWR_EPD: 10K; ERA-1AEB3401C_0201
R_TYPE_SEL: 2.2; ERA-1AEB3401C_0201
SJ1: ESP32_C6_LIBRARY_7_JUMPER_SJ
SW_DN: 2025-10-22_07-23-44_LIBRARY_EVP-AKE31ASW_EVP-AKE3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; 2025-10-22_07-23-44_LIBRARY_SW_EVP-AKE31A_PAN
SW_NET: 2025-10-22_07-23-44_LIBRARY_EVP-AKE31ASW_EVP-AKE3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; 2025-10-22_07-23-44_LIBRARY_SW_EVP-AKE31A_PAN
SW_UP: 2025-10-22_07-23-44_LIBRARY_EVP-AKE31ASW_EVP-AKE3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; 2025-10-22_07-23-44_LIBRARY_SW_EVP-AKE31A_PAN
TP_3.3V, TP_3V3: HECTOR_WATCH_1_TPTP20R; HECTOR_WATCH_1_TP20R
TP_BAT_GND: HECTOR_WATCH_1_TPTP20R; HECTOR_WATCH_1_TP20R
TP_GND: HECTOR_WATCH_1_TPTP20R; HECTOR_WATCH_1_TP20R
TP_ON: HECTOR_WATCH_1_TPTP20R; HECTOR_WATCH_1_TP20R
TP_OP: HECTOR_WATCH_1_TPTP20R; HECTOR_WATCH_1_TP20R
TP_RESET: HECTOR_WATCH_1_TPTP20R; HECTOR_WATCH_1_TP20R
TP_SCL: HECTOR_WATCH_1_TPTP20R; HECTOR_WATCH_1_TP20R
TP_SDA: HECTOR_WATCH_1_TPTP20R; HECTOR_WATCH_1_TP20R
TP_SWDCLK: HECTOR_WATCH_1_TPTP20R; HECTOR_WATCH_1_TP20R
TP_SWDIO: HECTOR_WATCH_1_TPTP20R; HECTOR_WATCH_1_TP20R
TP_SWO: HECTOR_WATCH_1_TPTP20R; HECTOR_WATCH_1_TP20R
TP_VBAT: HECTOR_WATCH_1_TPTP20R; HECTOR_WATCH_1_TP20R
TP_VREG: HECTOR_WATCH_1_TPTP20R; HECTOR_WATCH_1_TP20R
U1: NRF52840_QF; NORDIC_NRF_4_AQFN50P700X700X85_HS-74N
U3: MAX17048G+T10; ESP32_C6_LIBRARY_SON50P200X200X80-9N
X1: 32MHz; NORDIC_NRF_BT-XTAL_2016_N
X2: 32.768kHz; NORDIC_NRF_1_XTAL_3215_N

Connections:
3V3: C6.1, C7.1, C8.1, C12.1, C14.1, C19.1, C25.1, C33.1, C34.2, IC2.C2 (VDD), IC3.3 (VDDIO), IC3.7 (VDD), IC3.10 (CSB), IC9.E2 (VOUT_1), IC9.E3 (VOUT_2), J2.1, Q1.2 (S), R5.2, R7.2, R8.2, R17.1, R18.1, R_PWR_EPD.2, TP_3.3V.TP, TP_3V3.TP, U1.P$A22 (VDD), U1.P$AD14 (VDD), U1.P$AD23 (VDD), U1.P$B1 (VDD), U1.P$W1 (VDD), U1.P$Y2 (VDDH)
ALERT: U1.P$J24 (P0.10/NFC2), U3.5 (!ALERT)
D+: D3.4 (I/O2_2), U1.P$AD6 (D+)
D-: D3.6 (I/O1_2), U1.P$AD4 (D-)
DN: D3.1 (I/O1_1), J4.A7 (DN1), J4.B7 (DN2)
DP: D3.3 (I/O2_1), J4.A6 (DP1), J4.B6 (DP2)
EPD_3V3: C1-EP-DR.1, EPD_C5.2, J1.15, J1.16, L5.2, Q1.3 (D)
EPD_BUSY: J1.9
EPD_CS: J1.12, U1.P$K2 (P0.05/AIN3)
EPD_DC: J1.11, U1.P$AD10 (P0.15)
EPD_RST: J1.10, U1.P$AC11 (P0.16)
EPS_BUSY: U1.P$AD12 (P0.17)
GDR: J1.2, Q3.1 (G), R2-EP-DR.2
GND: C1.2, C1-EP-DR.2, C2.2, C3.2, C4.2, C5.2, C6.2, C7.2, C8.2, C9.2, C10.2, C11.2, C12.2, C13.2, C14.2, C15.2, C16.2, C17.1, C18.1, C19.2, C20.2, C21.2, C22.2, C23.1, C24.1, C25.2, C27.1, C29.2, C30.2, C31.2, C32.2, C33.2, C34.1, C37.2, C38.1, C39.2, C42.2, C43.2, D3.2 (GND), D4.1 (K), EPD_C1.1, EPD_C2.1, EPD_C5.1, EPD_C6.1, EPD_C7.1, EPD_C8.1, EPD_C9.1, EPD_C10.1, EPD_C11.1, EPD_C12.1, IC1.D2 (GND), IC2.B1 (IN/TRIG), IC2.B3 (GND), IC3.8 (GNDIO), IC3.9 (GND), IC9.B1 (VSEL), IC9.C1 (AGND), IC9.C2 (PGND_1), IC9.C3 (PGND_2), J1.8, J1.17, J1.MP1, J1.MP2, J2.3, J2.5, J4.A1_B12 (GND), J4.A12_B1 (GND), J4.SH1 (SHIELD), J4.SH2 (SHIELD), J4.SH3 (SHIELD), J4.SH4 (SHIELD), R1_USB.1, R2-EP-DR.1, R2_USB.2, R3.1, R9.1, R_TYPE_SEL.1, SJ1.1, SW_DN.1, SW_NET.1, SW_UP.1, TP_BAT_GND.TP, TP_GND.TP, U1.P$74 (VSS_PAD), U1.P$75 (VSS_PAD), U1.P$76 (VSS_PAD), U1.P$77 (VSS_PAD), U1.P$78 (VSS_PAD), U1.P$79 (VSS_PAD), U1.P$80 (VSS_PAD), U1.P$81 (VSS_PAD), U1.P$82 (VSS_PAD), U1.P$83 (VSS_PAD), U1.P$84 (VSS_PAD), U1.P$85 (VSS_PAD), U1.P$86 (VSS_PAD), U1.P$87 (VSS_PAD), U1.P$88 (VSS_PAD), U1.P$89 (VSS_PAD), U1.P$90 (VSS_PAD), U1.P$B7 (VSS), U1.P$F23 (VSS_PA), U3.1 (CTG), U3.4 (GND), U3.6 (QSTRT), U3.9 (EP), X1.2, X1.4
HAPTIC_EN: IC2.A1 (EN), U1.P$U1 (P0.12)
IMU_INT1: IC3.5 (INT1), U1.P$N1 (P0.08)
IMU_INT2: IC3.6 (INT2), U1.P$P2 (P1.08)
LX1: IC9.B2 (SW1_1), IC9.B3 (SW1_2), L7.1
LX2: IC9.D2 (SW2_1), IC9.D3 (SW2_2), L7.2
MOSI: J1.14, U1.P$B13 (P0.03/AIN1)
unnamed: C39.1, IC1.B2 (SYS)
unnamed: C5.1, U1.P$C1 (DEC1)
unnamed: IC9.D1 (SCL), R4.2
unnamed: IC9.E1 (SDA), R2.2
unnamed: C17.2, U1.P$D2 (P0.00/XL1), X2.1
unnamed: IC1.D1 (TS/MR), R9.2
unnamed: ANT1.1 (FEED), C4.1, C22.1, L1.2
unnamed: EPD_C8.2, J1.20
unnamed: L2.1, U1.P$B3 (DCC)
unnamed: IC3.1 (SDO), R3.2
unnamed: C10.1, C15.1, C16.1, L3.2, U1.P$B5 (DEC4), U1.P$E24 (DEC6)
unnamed: L2.2, L3.1
unnamed: C18.2, U1.P$F2 (P0.01/XL2), X2.2
unnamed: C2-EP-DR.2, D5.2 (A), L5.1, Q3.3 (D)
unnamed: C2-EP-DR.1, D2.1 (K), D4.2 (A)
unnamed: EPD_C2.2, J1.4
unnamed: R1-EP-DR.1, R_TYPE_SEL.2, SJ1.2
unnamed: EPD_C12.2, J1.24
unnamed: C9.1, U1.P$N24 (DEC5)
unnamed: EPD_C1.2, J1.5
unnamed: C20.1, U1.P$AC5 (DEC3V3)
unnamed: J4.A5 (CC1), R1_USB.2
unnamed: C3.1, L1.1, U1.P$H23 (ANT)
unnamed: EPD_C10.2, J1.22
unnamed: C11.1, U1.P$D23 (DEC3)
unnamed: C1.1, U1.P$B24 (XC1), X1.1
unnamed: C2.1, U1.P$A23 (XC2), X1.3
unnamed: C32.1, IC2.A2 (REG)
unnamed: C13.1, U1.P$A18 (DEC2)
unnamed: J4.B5 (CC2), R2_USB.1
unnamed: EPD_C6.2, J1.18
unnamed: EPD_C7.2, J1.19
OUT+: IC2.A3 (OUT+), TP_OP.TP
OUT-: IC2.C3 (OUT-), TP_ON.TP
P0.04: U1.P$J1 (P0.04/AIN2)
P0.09: U1.P$L24 (P0.09/NFC1)
P0.13: C30.1, R5.1, SW_UP.2, U1.P$AD8 (P0.13)
P0.14: C31.1, R8.1, SW_NET.2, U1.P$AC9 (P0.14)
P0.19: U1.P$AC15 (P0.19)
P0.20: U1.P$AD16 (P0.20)
P0.21: U1.P$AC17 (P0.21)
P0.22: U1.P$AD18 (P0.22)
P0.23: U1.P$AC19 (P0.23)
P0.24: U1.P$AD20 (P0.24)
P0.25: U1.P$AC21 (P0.25)
P0.26: U1.P$G1 (P0.26)
P0.27: U1.P$H2 (P0.27)
P0.28: U1.P$B11 (P0.28/AIN4)
P0.29: U1.P$A10 (P0.29/AIN5)
P0.30: U1.P$B9 (P0.30/AIN6)
P0.31: U1.P$A8 (P0.31/AIN7)
P1.01: Q1.1 (G), R_PWR_EPD.1, U1.P$Y23 (P1.01)
P1.02: C29.1, R7.1, SW_DN.2, U1.P$W24 (P1.02)
P1.03: U1.P$V23 (P1.03)
P1.04: U1.P$U24 (P1.04)
P1.05: U1.P$T23 (P1.05)
P1.06: U1.P$R24 (P1.06)
P1.07: U1.P$P23 (P1.07)
P1.09: U1.P$R1 (P1.09)
P1.10: U1.P$A20 (P1.10)
P1.11: U1.P$B19 (P1.11)
P1.12: U1.P$B17 (P1.12)
P1.13: U1.P$A16 (P1.13)
P1.14: U1.P$B15 (P1.14)
P1.15: U1.P$A14 (P1.15)
PMIC_INT: IC1.A1 (!INT), U1.P$T2 (P0.11)
PREVGH: D5.1 (K), EPD_C9.2, J1.21
PREVGL: D2.2 (A), EPD_C11.2, J1.23
RESE: J1.3, Q3.2 (S), R1-EP-DR.2
RESET: J2.6, TP_RESET.TP, U1.P$AC13 (P0.18/RESET)
SCK: J1.13, U1.P$A12 (P0.02/AIN0)
SCL: IC1.B1 (SCL), IC2.C1 (SCL), IC3.12 (SCX), R4.1, R17.2, TP_SCL.TP, U1.P$M2 (P0.07), U3.7 (SCL)
SDA: IC1.C1 (SDA), IC2.B2 (SDA), IC3.2 (SDX), R2.1, R18.2, TP_SDA.TP, U1.P$L1 (P0.06), U3.8 (SDA)
SWDCLK: J2.4, TP_SWDCLK.TP, U1.P$AA24 (SWDCLK)
SWDIO: J2.2, TP_SWDIO.TP, U1.P$AC24 (SWDIO)
SWO: TP_SWO.TP, U1.P$AD22 (P1.00)
VBAT: C27.2, C37.1, IC1.C2 (BAT), TP_VBAT.TP, U3.2 (CELL), U3.3 (VDD)
VBUS: C21.1, C38.2, C42.1, C43.1, D3.5 (VBUS), IC1.A2 (IN), J4.A4_B9 (VBUS), J4.A9_B4 (VBUS), U1.P$AD2 (VBUS)
VREG: C23.2, C24.2, IC9.A1 (EN), IC9.A2 (VIN_1), IC9.A3 (VIN_2), TP_VREG.TP

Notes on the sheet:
USB C Connector & ESD Protection
Fuel Gauge
Buttons
Haptic Driver
E-Paper Display Connector
E-Paper Drive Circuit
IMU
SWD
DC/DC
LiPo Charger

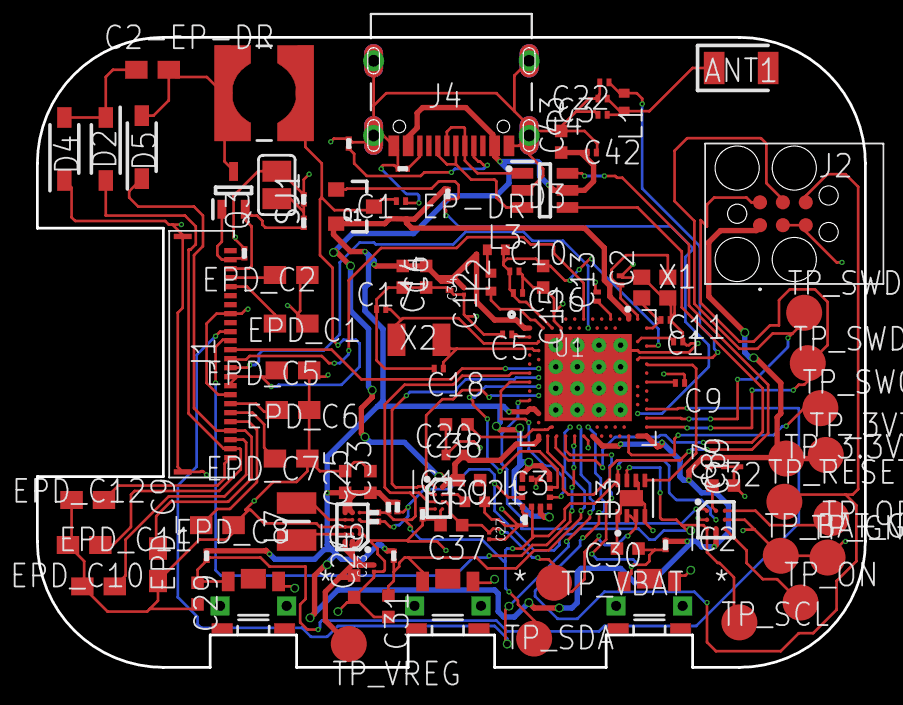
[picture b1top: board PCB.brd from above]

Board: 4 copper layers, 46.0 x 35.0 mm, 105 parts (0 on the bottom side), 70 nets.

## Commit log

2026-04-10 Create project_2026
2026-04-10 Add new content to project_2026
2026-04-10 Create skdf
2026-04-10 Create Pick and Place
2026-04-10 Rename Pick_and_place.cpl to Pick and place.cpl
2026-04-10 Rename Bill _of_Materials.bom to Bill of Materials.bom
2026-04-17 Add files via upload
    schematic final - modificare denumire label
2026-04-17 pcb final
    modificare rutare
2026-04-21 varianta finala
2026-04-21 update pentru frame
    adaugare frame schematic
2026-04-21 Mechanical directory
2026-04-21 write README.md
2026-04-21 Create l
2026-04-21 Add GNU General Public License version 2
2026-04-21 carcasa
2026-04-21 arhiva .step

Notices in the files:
parts and their libraries:
COPYRIGHT: Copyright (C) 2024 Ultra Librarian. All rights reserved.
COPYRIGHT: Copyright (C) 2025 Ultra Librarian. All rights reserved.
